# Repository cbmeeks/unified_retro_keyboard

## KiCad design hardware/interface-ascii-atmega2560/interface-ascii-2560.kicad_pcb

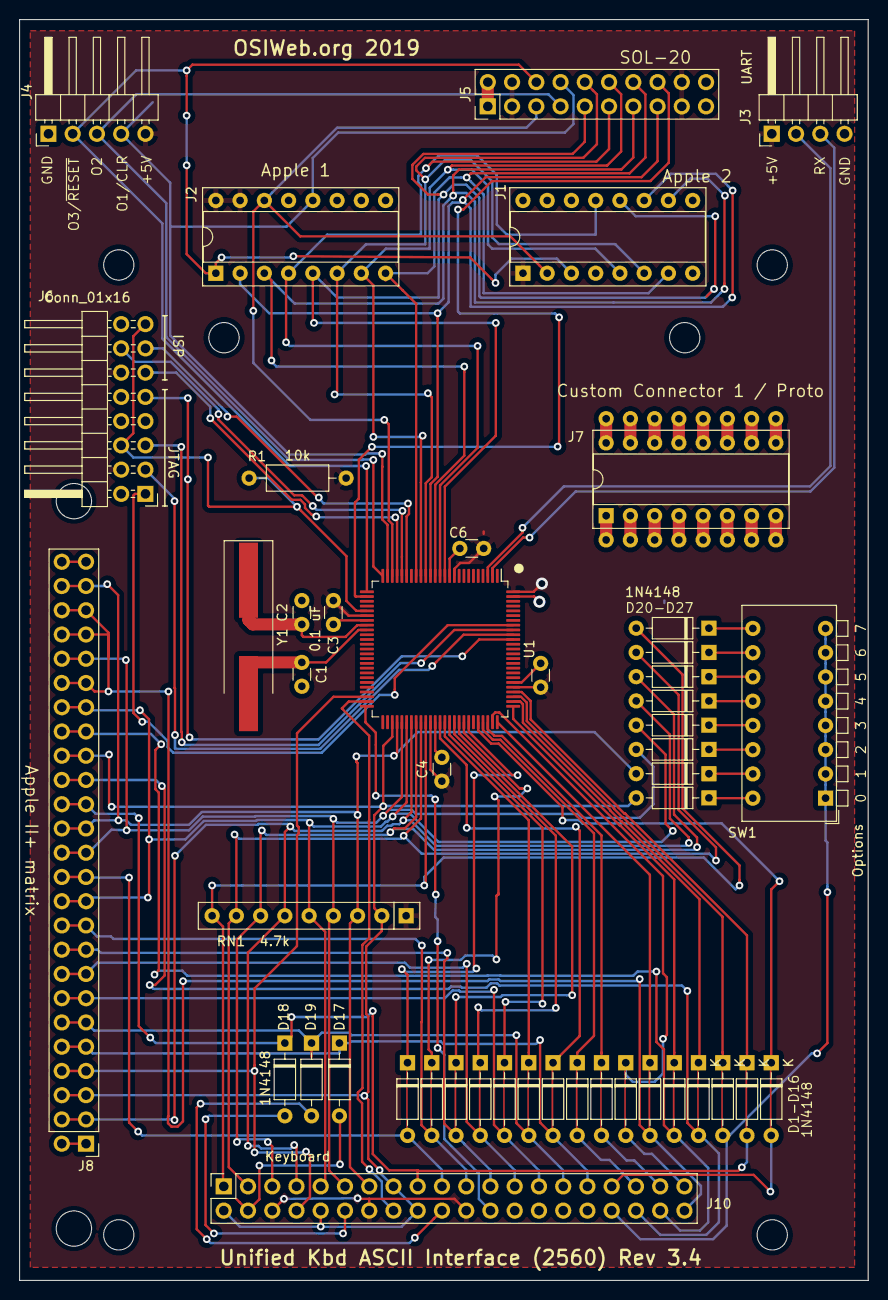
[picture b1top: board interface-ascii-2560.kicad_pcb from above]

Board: 2 copper layers, 88.9 x 132.1 mm, 49 parts (0 on the bottom side), 80 nets.

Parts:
C1, C2: 36pf; C_Disc_D3.0mm_W1.6mm_P2.50mm
C3, C4, C5, C6: 0.1 uF; C_Disc_D3.0mm_W1.6mm_P2.50mm
D1, D2, D3, D4, D5, D6, D7, D8, D9, D10, D11, D12, D13, D14, D15, D16: 1N4148; D_DO-35_SOD27_P7.62mm_Horizontal_bypassed
D17, D18, D19, D20, D21, D22, D23, D24, D25, D26, D27: 1N4148; D_DO-35_SOD27_P7.62mm_Horizontal
J1: Apple 2; DIP-16_W7.62mm_Socket
J2: Apple 1; DIP-16_W7.62mm_Socket
J3: UART; PinHeader_1x04_P2.54mm_Horizontal
J4: Conn_01x05; PinHeader_1x05_P2.54mm_Horizontal
J5: SOL-20; SOL20-header-vertical
J6: Conn_01x16; PinHeader_2x08_P2.54mm_Horizontal
J7: Custom Connector 1 / Proto; DIP-16_W7.62mm_Proto
J8: Apple II+ matrix; ExpansionHeader_1x25_P2.54
J10: Keyboard; PinHeader_2x20_P2.54mm_Vertical
MH1, MH2: Apple II; MountingHole_3.7mm
R1: 10k; R_Axial_DIN0207_L6.3mm_D2.5mm_P10.16mm_Horizontal
RN1: 4.7k; R_Array_SIP9
SW1: Options; SW_DIP_SPSTx08_Piano_CTS_Series194-8MSTN_W7.62mm_P2.54mm
U1: ATmega2560-16AU; TQFP-100_14x14mm_P0.5mm
Y1: 16.000 MHz; Crystal_SMD_HC49-SD_HandSoldering

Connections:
/Col0: D20.2, J8.3, J8.17, J10.2, J10.10, J10.15, J10.18, RN1.2, U1.53
/Col1: D24.2, J8.14, J8.24, J10.13, RN1.3, U1.54
/Col2: D21.2, J8.13, J8.21, J10.11, RN1.4, U1.55
/Col3: D25.2, J8.11, J8.19, J10.9, RN1.5, U1.56
/Col4: D22.2, J8.2, J10.7, RN1.6, U1.57
/Col5: D26.2, J10.5, RN1.7, U1.58
/Col6: D23.2, J10.3, RN1.8, U1.59
/Col7: D27.2, J10.1, RN1.9, U1.60
/D0: J1.12, J2.5, J5.5, U1.12
/D1: J1.13, J2.4, J5.6, U1.13
/D2: J1.10, J2.3, J5.7, U1.14
/D3: J1.11, J2.2, J5.8, U1.15
/D4: J1.6, J2.6, J5.15, U1.16
/D5: J1.5, J2.7, J5.16, U1.17
/D6: J1.7, J2.8, J5.17, U1.18
/D7: J5.18, U1.27
/LED1: J8.4, J10.8, U1.48
/LED2: J10.16, U1.49
/LED3: J10.24, U1.50
/MISO: J6.11, U1.22
/MOSI: J6.14, U1.21
/OUT1: J2.12, J4.4, J5.14, U1.24
/OUT2: J4.3, J5.4, U1.25
/OUT3: J1.3, J2.1, J4.2, J5.13, U1.26
/Row0: D9.2, D17.1, J8.5, J10.31
/Row1: D1.2, D19.1, J8.6, J10.29
/Row2: D10.2, J8.7, J10.27
/Row3: D2.2, J8.8, J10.25
/Row4: D11.2, J8.9, J10.23
/Row5: D3.2, J8.10, J10.21
/Row6: D12.2, J8.12, J10.19
/Row7: D4.2, D18.1, J8.15, J10.17
/Row8: D13.2, J10.34, SW1.1, SW1.2, SW1.3, SW1.4, SW1.5, SW1.6, SW1.7, SW1.8
/Row9: D5.2, J8.16, J10.36
/Row10: D14.2, J8.18, J10.38
/Row11: D6.2, J8.20, J8.22, J8.23, J10.40
/Row12: D15.2, J10.39
/Row13: D7.2, J10.37
/Row14: D16.2, J10.35
/Row15: D8.2, J10.33
/Rx: J3.3, U1.2
/SCK: J6.13, U1.20
/TCK: J6.1, U1.93
/TDI: J6.9, U1.90
/TDO: J6.3, U1.91
/TMS: J6.5, U1.92
/Tx: J3.2, U1.3
/~RESET: J6.6, J6.15, R1.2, U1.30
/~STROBE: J1.2, J2.14, J5.3, U1.23
GND: C1.2, C2.2, C3.2, C4.2, C5.2, C6.2, J1.8, J2.9, J3.4, J4.1, J5.1, J5.10, J5.11, J5.20, J6.2, J6.10, J6.16, U1.11, U1.32, U1.62, U1.81, U1.99
unnamed: C1.1, U1.34, Y1.2
unnamed: C2.1, U1.33, Y1.1
unnamed: D1.1, U1.64
unnamed: D2.1, U1.66
unnamed: D3.1, U1.68
unnamed: D4.1, U1.79
unnamed: D5.1, U1.77
unnamed: D6.1, U1.75
unnamed: D7.1, U1.73
unnamed: D8.1, U1.71
unnamed: D9.1, U1.63
unnamed: D10.1, U1.65
unnamed: D11.1, U1.67
unnamed: D12.1, U1.69
unnamed: D13.1, U1.78
unnamed: D14.1, U1.76
unnamed: D15.1, U1.74
unnamed: D16.1, U1.72
unnamed: D17.2, J10.4
unnamed: D18.2, J10.12
unnamed: D19.2, J10.20
unnamed: D20.1, SW1.16
unnamed: D21.1, SW1.14
unnamed: D22.1, SW1.12
unnamed: D23.1, SW1.10
unnamed: D24.1, SW1.15
unnamed: D25.1, SW1.13
unnamed: D26.1, SW1.11
unnamed: D27.1, SW1.9
VCC: C3.1, C4.1, C5.1, C6.1, J1.1, J2.15, J2.16, J3.1, J4.5, J5.2, J5.9, J5.12, J5.19, J6.4, J6.12, J10.6, J10.14, J10.22, R1.1, RN1.1, U1.10, U1.31, U1.61, U1.80, U1.100

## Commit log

2020-06-03 Add wiring for apple-II two-piece encoder replacement
2020-06-03 Remove extraneous silk screen text
2020-06-03 Add apple 2 encoder board (pre-customized ASCII Interface (2560)
